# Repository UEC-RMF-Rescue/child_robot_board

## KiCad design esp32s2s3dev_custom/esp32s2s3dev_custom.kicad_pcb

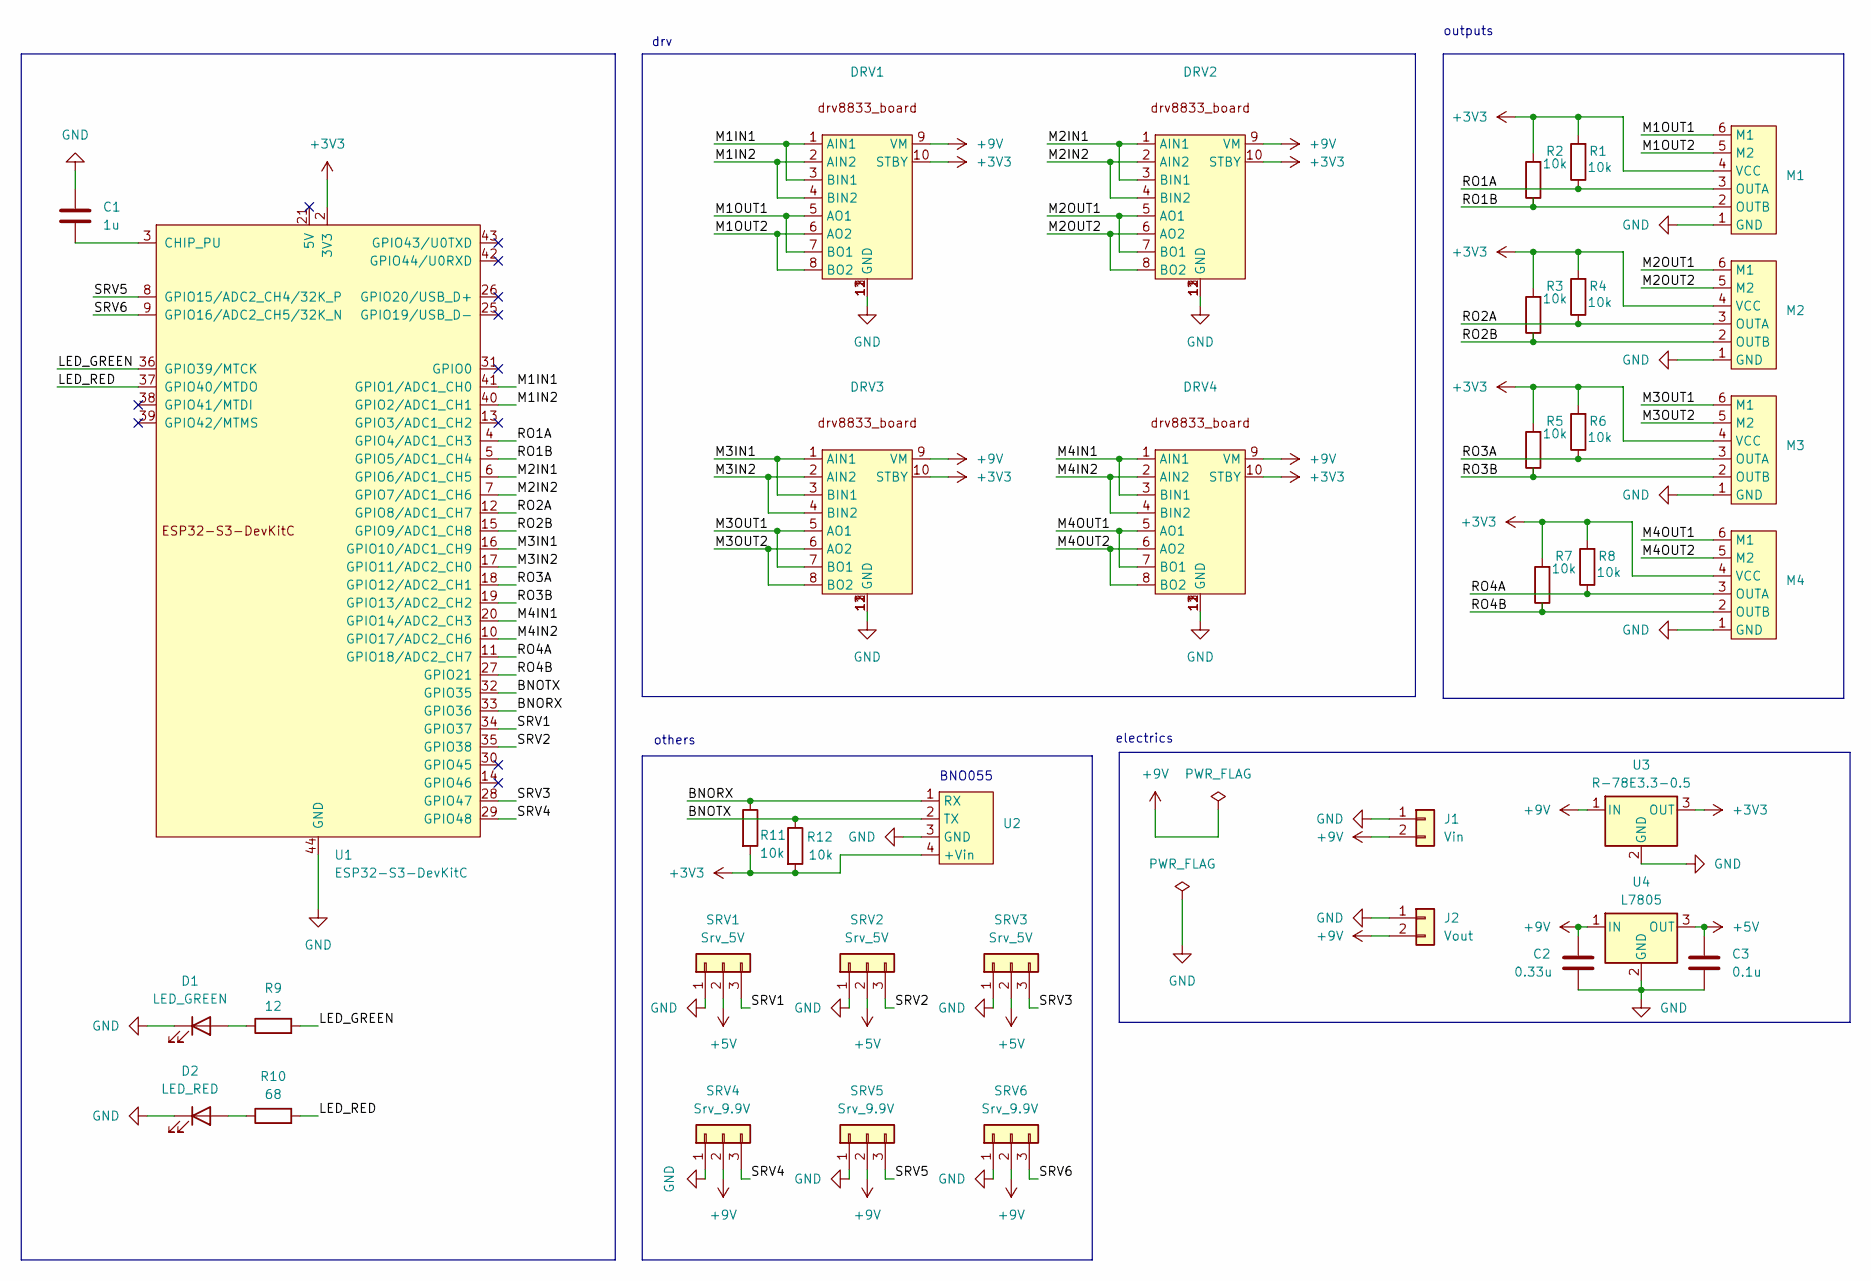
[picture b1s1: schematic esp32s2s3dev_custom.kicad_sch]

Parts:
C1: 1u; C_Disc_D3.0mm_W1.6mm_P2.50mm
C2: 0.33u; C_Disc_D3.0mm_W1.6mm_P2.50mm
C3: 0.1u; C_Disc_D3.0mm_W1.6mm_P2.50mm
D1: LED_GREEN; LED_D3.0mm_Clear
D2: LED_RED; LED_D3.0mm
DRV1, DRV2, DRV3, DRV4: drv8833_board
J1: Vin; JST_VH_B2P-VH_1x02_P3.96mm_Vertical
J2: Vout; JST_VH_B2P-VH_1x02_P3.96mm_Vertical
M1, M2, M3, M4: JST_EH_B6B-EH-A_1x06_P2.50mm_Vertical
R1, R2, R3, R4, R5, R6, R7, R8, R11, R12: 10k; R_Axial_DIN0204_L3.6mm_D1.6mm_P5.08mm_Horizontal
R9: 12; R_Axial_DIN0204_L3.6mm_D1.6mm_P5.08mm_Horizontal
R10: 68; R_Axial_DIN0204_L3.6mm_D1.6mm_P7.62mm_Horizontal
SRV1, SRV2, SRV3: Srv_5V; PinHeader_1x03_P1.27mm_Vertical
SRV4, SRV5, SRV6: Srv_9.9V; PinHeader_1x03_P1.27mm_Vertical
U1: ESP32-S3-DevKitC
U2: bno055_board
U3: R-78E3.3-0.5; Converter_DCDC_RECOM_R-78E-0.5_THT
U4: L7805

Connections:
+3V3: DRV1.10 (STBY), DRV2.10 (STBY), DRV3.10 (STBY), DRV4.10 (STBY), M1.4 (VCC), M2.4 (VCC), M3.4 (VCC), M4.4 (VCC), R1.2, R2.2, R3.2, R4.2, R5.2, R6.2, R7.2, R8.2, R11.2, R12.2, U1.1 (3V3), U1.2 (3V3), U2.4 (+Vin), U3.3 (OUT)
+5V: C3.1, SRV1.2, SRV2.2, SRV3.2, U4.3 (OUT)
+9V: C2.2, DRV1.9 (VM), DRV2.9 (VM), DRV3.9 (VM), DRV4.9 (VM), J1.2, J2.2, SRV4.2, SRV5.2, SRV6.2, U3.1 (IN), U4.1 (IN)
/BNORX: R11.1, U1.33 (GPIO36), U2.1 (RX)
/BNOTX: R12.1, U1.32 (GPIO35), U2.2 (TX)
/LED_GREEN: R9.2, U1.36 (GPIO39/MTCK)
/LED_RED: R10.2, U1.37 (GPIO40/MTDO)
/M1IN1: DRV1.1 (AIN1), DRV1.3 (BIN1), U1.41 (GPIO1/ADC1_CH0)
/M1IN2: DRV1.2 (AIN2), DRV1.4 (BIN2), U1.40 (GPIO2/ADC1_CH1)
/M1OUT1: DRV1.5 (AO1), DRV1.7 (BO1), M1.6 (M1)
/M1OUT2: DRV1.6 (AO2), DRV1.8 (BO2), M1.5 (M2)
/M2IN1: DRV2.1 (AIN1), DRV2.3 (BIN1), U1.6 (GPIO6/ADC1_CH5)
/M2IN2: DRV2.2 (AIN2), DRV2.4 (BIN2), U1.7 (GPIO7/ADC1_CH6)
/M2OUT1: DRV2.5 (AO1), DRV2.7 (BO1), M2.6 (M1)
/M2OUT2: DRV2.6 (AO2), DRV2.8 (BO2), M2.5 (M2)
/M3IN1: DRV3.1 (AIN1), DRV3.3 (BIN1), U1.16 (GPIO10/ADC1_CH9)
/M3IN2: DRV3.2 (AIN2), DRV3.4 (BIN2), U1.17 (GPIO11/ADC2_CH0)
/M3OUT1: DRV3.5 (AO1), DRV3.7 (BO1), M3.6 (M1)
/M3OUT2: DRV3.6 (AO2), DRV3.8 (BO2), M3.5 (M2)
/M4IN1: DRV4.1 (AIN1), DRV4.3 (BIN1), U1.20 (GPIO14/ADC2_CH3)
/M4IN2: DRV4.2 (AIN2), DRV4.4 (BIN2), U1.10 (GPIO17/ADC2_CH6)
/M4OUT1: DRV4.5 (AO1), DRV4.7 (BO1), M4.6 (M1)
/M4OUT2: DRV4.6 (AO2), DRV4.8 (BO2), M4.5 (M2)
/RO1A: M1.3 (OUTA), R1.1, U1.4 (GPIO4/ADC1_CH3)
/RO1B: M1.2 (OUTB), R2.1, U1.5 (GPIO5/ADC1_CH4)
/RO2A: M2.3 (OUTA), R4.1, U1.12 (GPIO8/ADC1_CH7)
/RO2B: M2.2 (OUTB), R3.1, U1.15 (GPIO9/ADC1_CH8)
/RO3A: M3.3 (OUTA), R6.1, U1.18 (GPIO12/ADC2_CH1)
/RO3B: M3.2 (OUTB), R5.1, U1.19 (GPIO13/ADC2_CH2)
/RO4A: M4.3 (OUTA), R8.1, U1.11 (GPIO18/ADC2_CH7)
/RO4B: M4.2 (OUTB), R7.1, U1.27 (GPIO21)
/SRV1: SRV1.3, U1.34 (GPIO37)
/SRV2: SRV2.3, U1.35 (GPIO38)
/SRV3: SRV3.3, U1.28 (GPIO47)
/SRV4: SRV4.3, U1.29 (GPIO48)
/SRV5: SRV5.3, U1.8 (GPIO15/ADC2_CH4/32K_P)
/SRV6: SRV6.3, U1.9 (GPIO16/ADC2_CH5/32K_N)
GND: C1.1, C2.1, C3.2, D1.1 (K), D2.1 (K), DRV1.11 (GND), DRV1.12, DRV1.13, DRV2.11 (GND), DRV2.12, DRV2.13, DRV3.11 (GND), DRV3.12, DRV3.13, DRV4.11 (GND), DRV4.12, DRV4.13, J1.1, J2.1, M1.1 (GND), M2.1 (GND), M3.1 (GND), M4.1 (GND), SRV1.1, SRV2.1, SRV3.1, SRV4.1, SRV5.1, SRV6.1, U1.22 (GND), U1.23 (GND), U1.24 (GND), U1.44 (GND), U2.3 (GND), U3.2 (GND), U4.2 (GND)
unnamed: D1.2 (A), R9.1
unnamed: D2.2 (A), R10.1
unnamed: C1.2, U1.3 (CHIP_PU)

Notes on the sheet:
outputs
drv
others
BNO055
electrics

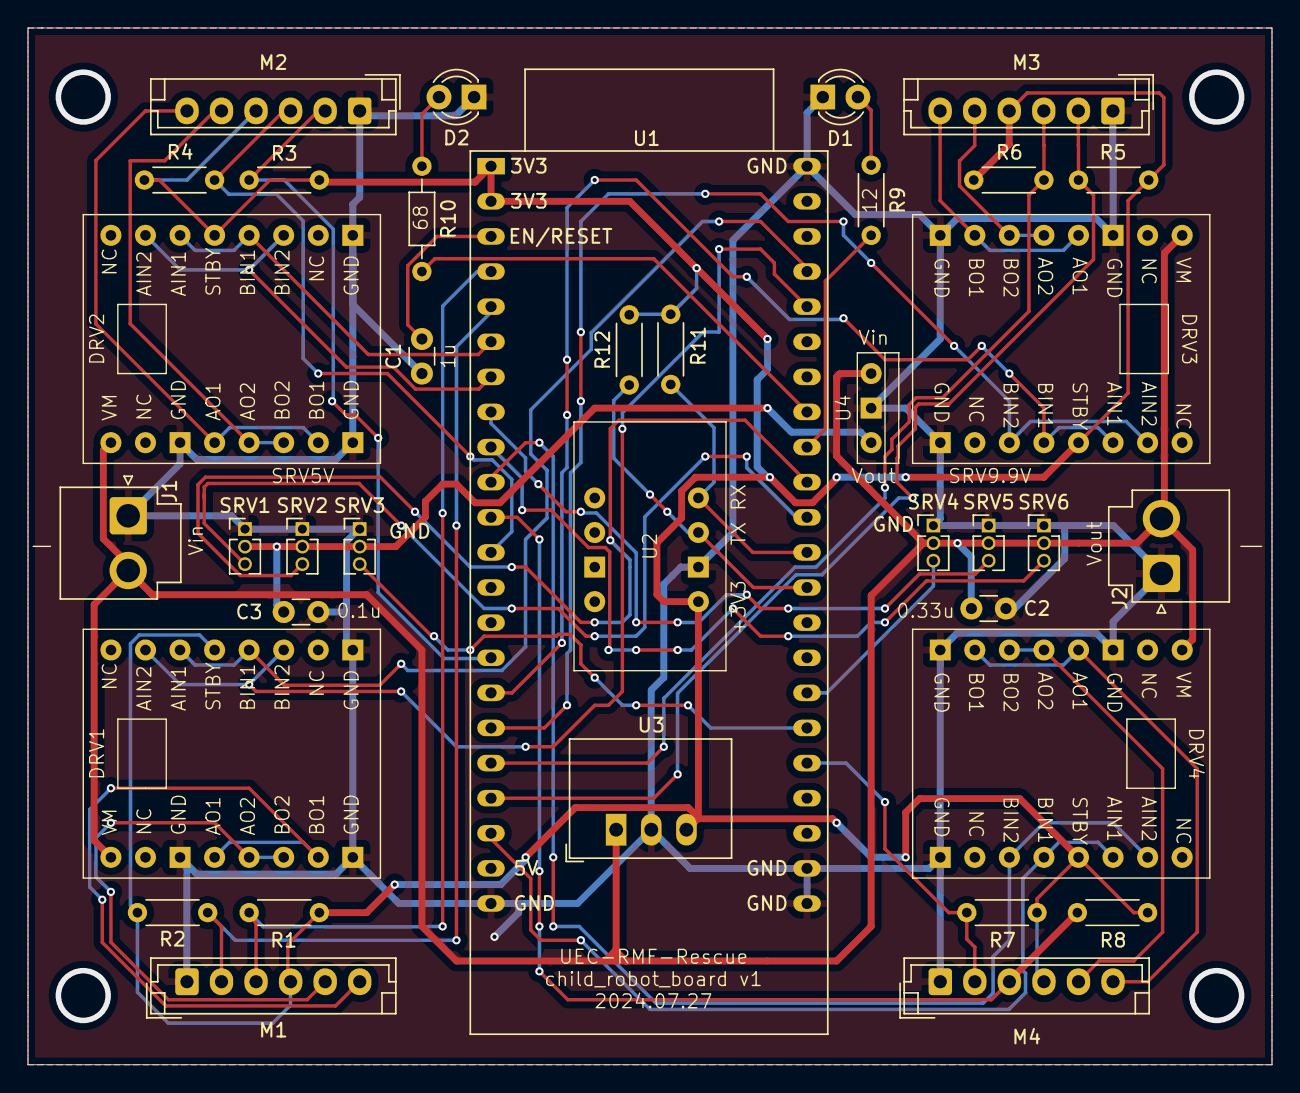
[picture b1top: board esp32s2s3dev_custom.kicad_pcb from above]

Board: 2 copper layers, 90.0 x 75.0 mm, 37 parts (0 on the bottom side), 41 nets.

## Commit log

2024-07-27 created first version of s3 custom
2024-07-27 add capacitor to registor, regulator to BNO serial
2024-07-27 changed some silkscreen
